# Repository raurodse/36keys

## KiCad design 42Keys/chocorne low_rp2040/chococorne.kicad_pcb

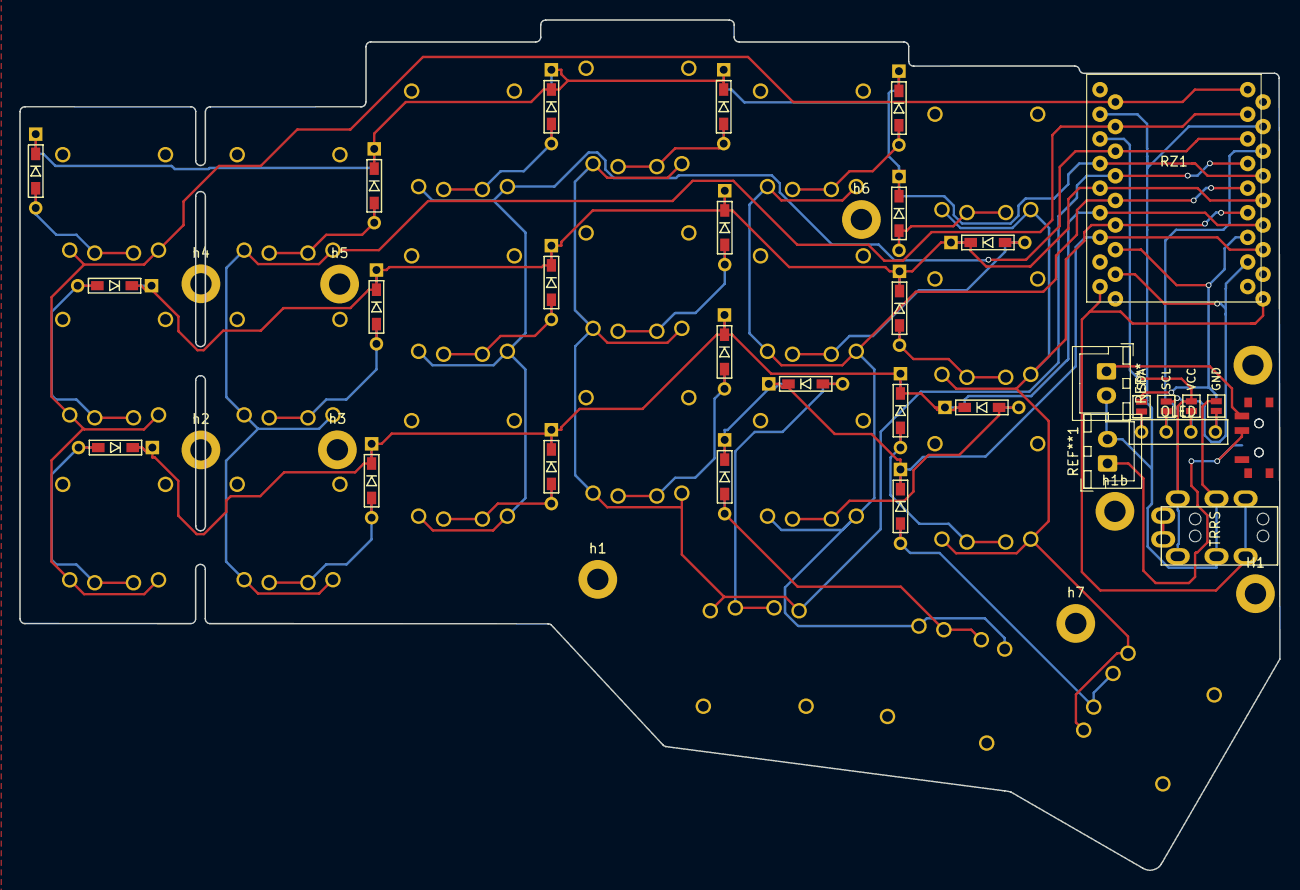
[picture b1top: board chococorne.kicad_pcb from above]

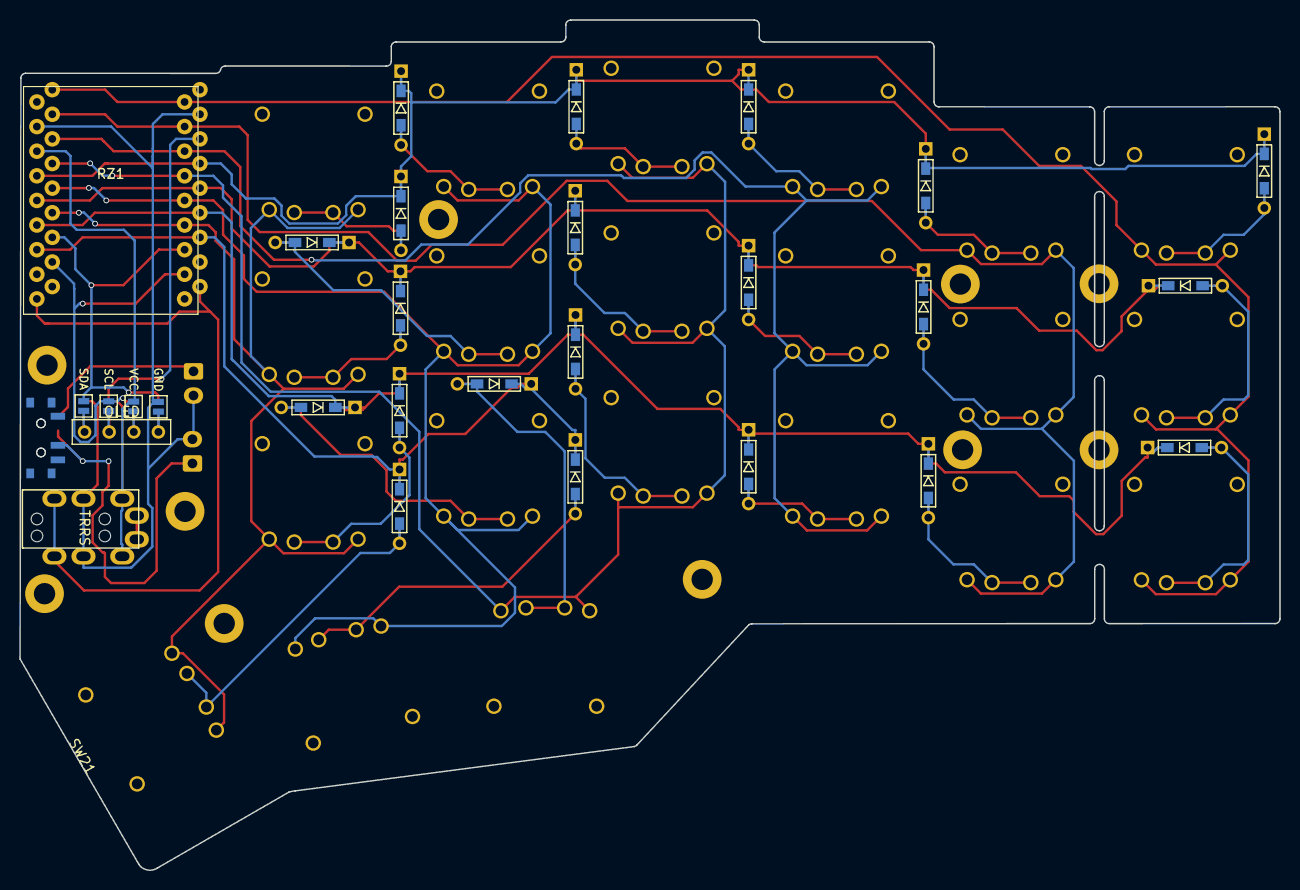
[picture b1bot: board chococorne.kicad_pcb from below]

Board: 2 copper layers, 130.0 x 87.7 mm, 65 parts (6 on the bottom side), 40 nets.

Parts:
D1, D2, D3, D4, D5, D6, D7, D8, D9, D10, D11, D12, D13, D14, D15, D16, D17, D18, D19, D20, D21: D; D3_TH_SMD
H1: h1; LEGO_HOLE
J1: MJ-4PP-9
J2: OLED
JP6, JP61: SDA; Jumper
JP62, JP68: GND; Jumper
JP63, JP66: SCL; Jumper
JP64, JP65: VCC; Jumper
RZ1, RZ1#2: RP2040-Zero
SW1, SW2, SW3, SW4, SW5, SW6, SW7, SW8, SW9, SW10, SW11, SW12, SW13, SW14, SW15, SW16, SW17, SW18, SW19, SW20, SW21: SW_PUSH; Kailh_PG1232
SW01, SW01#2: SW_SPDT; switch_SSSS811101
h1, h1b, h2, h3, h4, h5, h6, h7: h2; LEGO_HOLE

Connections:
GND: J1.C, JP62.1, JP68.1, RZ1.23 (GND), RZ1#2.23 (GND)
unnamed: D1.2, SW1.2
unnamed: D2.2, SW2.2
unnamed: D3.2 (A), SW3.2
unnamed: D4.2 (A), SW4.2
unnamed: D5.2 (A), SW5.2
unnamed: D6.2 (A), SW6.2
unnamed: D7.2, SW7.2
unnamed: D8.2, SW8.2
unnamed: D9.2 (A), SW9.2
unnamed: D10.2 (A), SW10.2
unnamed: D11.2 (A), SW11.2
unnamed: D12.2 (A), SW12.2
unnamed: D13.2, SW13.2
unnamed: D14.2, SW14.2
unnamed: D15.2 (A), SW15.2
unnamed: D16.2 (A), SW16.2
unnamed: D17.2 (A), SW17.2
unnamed: D18.2 (A), SW18.2
unnamed: D19.2 (A), SW19.2
unnamed: D20.2 (A), SW20.2
unnamed: D21.2 (A), SW21.2
unnamed: J2.3, JP65.2, JP66.2
unnamed: J2.4, JP6.2, JP68.2
unnamed: J2.2, JP63.2, JP64.2
unnamed: J2.1, JP61.2, JP62.2
SCL: JP63.1, JP66.1, RZ1.8 (GP7), RZ1#2.8 (GP7)
SDA: JP6.1, JP61.1, RZ1.7 (GP6), RZ1#2.7 (GP6)
VCC: J1.D, JP64.1, JP65.1, RZ1.21 (3V3), RZ1#2.21 (3V3)
col0: RZ1.1 (GP0), RZ1#2.1 (GP0), SW1.1, SW7.1, SW13.1
col1: RZ1.2 (GP1), RZ1#2.2 (GP1), SW2.1, SW8.1, SW14.1
col2: RZ1.3 (GP2), RZ1#2.3 (GP2), SW3.1, SW9.1, SW15.1
col3: RZ1.4 (GP3), RZ1#2.4 (GP3), SW4.1, SW10.1, SW16.1, SW19.1
col4: RZ1.5 (GP4), RZ1#2.5 (GP4), SW5.1, SW11.1, SW17.1, SW20.1
col5: RZ1.6 (GP5), RZ1#2.6 (GP5), SW6.1, SW12.1, SW18.1, SW21.1
data: J1.B, RZ1.15 (GP14), RZ1#2.15 (GP14)
row0: D1.1, D2.1, D3.1 (K), D4.1 (K), D5.1 (K), D6.1 (K), RZ1.20 (GP29), RZ1#2.20 (GP29)
row1: D7.1, D8.1, D9.1 (K), D10.1 (K), D11.1 (K), D12.1 (K), RZ1.19 (GP28), RZ1#2.19 (GP28)
row2: D13.1, D14.1, D15.1 (K), D16.1 (K), D17.1 (K), D18.1 (K), RZ1.18 (GP27), RZ1#2.18 (GP27)
row3: D19.1 (K), D20.1 (K), D21.1 (K), RZ1.17 (GP26), RZ1#2.17 (GP26)

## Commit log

2022-09-10 first version of rp2040 and seeeduino xiao nrf52840
2022-09-15 add switch and relocate pcb
2022-09-15 backup files
